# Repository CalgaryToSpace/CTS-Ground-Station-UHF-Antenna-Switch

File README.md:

# CTS-Ground-Station-UHF-Antenna-Switch

PCB and firmware for a ground station UHF antenna switch (between high-power uplink and low-noise downlink, via a single antenna).

This is a high-power UHF antenna switch PCB (for separate RX/TX paths), controlled with automatic TX sensing.

## Status

Rev 1 PCB works and is deployed at the CalgaryToSpace ground station as of 2026-05-26.

Rev 2 PCB is under development, though it is only a small incremental improvement over Rev 1. Main goal with Rev 2 is to improve the isolation performance.

## Render

See the Releases for schematics, gerbers, and BOM.

## Features

* High Power: Supports TX power of >45 dBm (>30 W)
* Low insertion loss
* Automatic carrier sensing on the TX line (easy to deploy)
* Shunt-to-GND: Avoids damage to the transmitter by avoiding reflecting any power back on the TX port, in case of switching latency or failure. Dissipates as heat through a dummy load.
* LED indicators.
* Uses RF relays for switching. Simple design and minimal power supply requirements, compared to PIN Diode alternative approach.
* Logs via USB serial interface.
* Optional slide switch to override control modes.
* Optional control via USB serial interface overrides.

## Key Components

* RF Relay: `1462051-1` (`HF3-1` with 3V control, aka `HF3-51`)
* Dummy Load Resistor: `I100N50X4B`
* RF Attenuator (10 dB): `PAT1220-C-10DB-T5`
* RF Detector: `LTC5507ES6`
* Microcontroller: RP2040-Zero PCB

## License

* **Hardware Parts:** CERN Open Hardware Licence Version 2 - Permissive
* **Firmware:** Apache 2.0 License

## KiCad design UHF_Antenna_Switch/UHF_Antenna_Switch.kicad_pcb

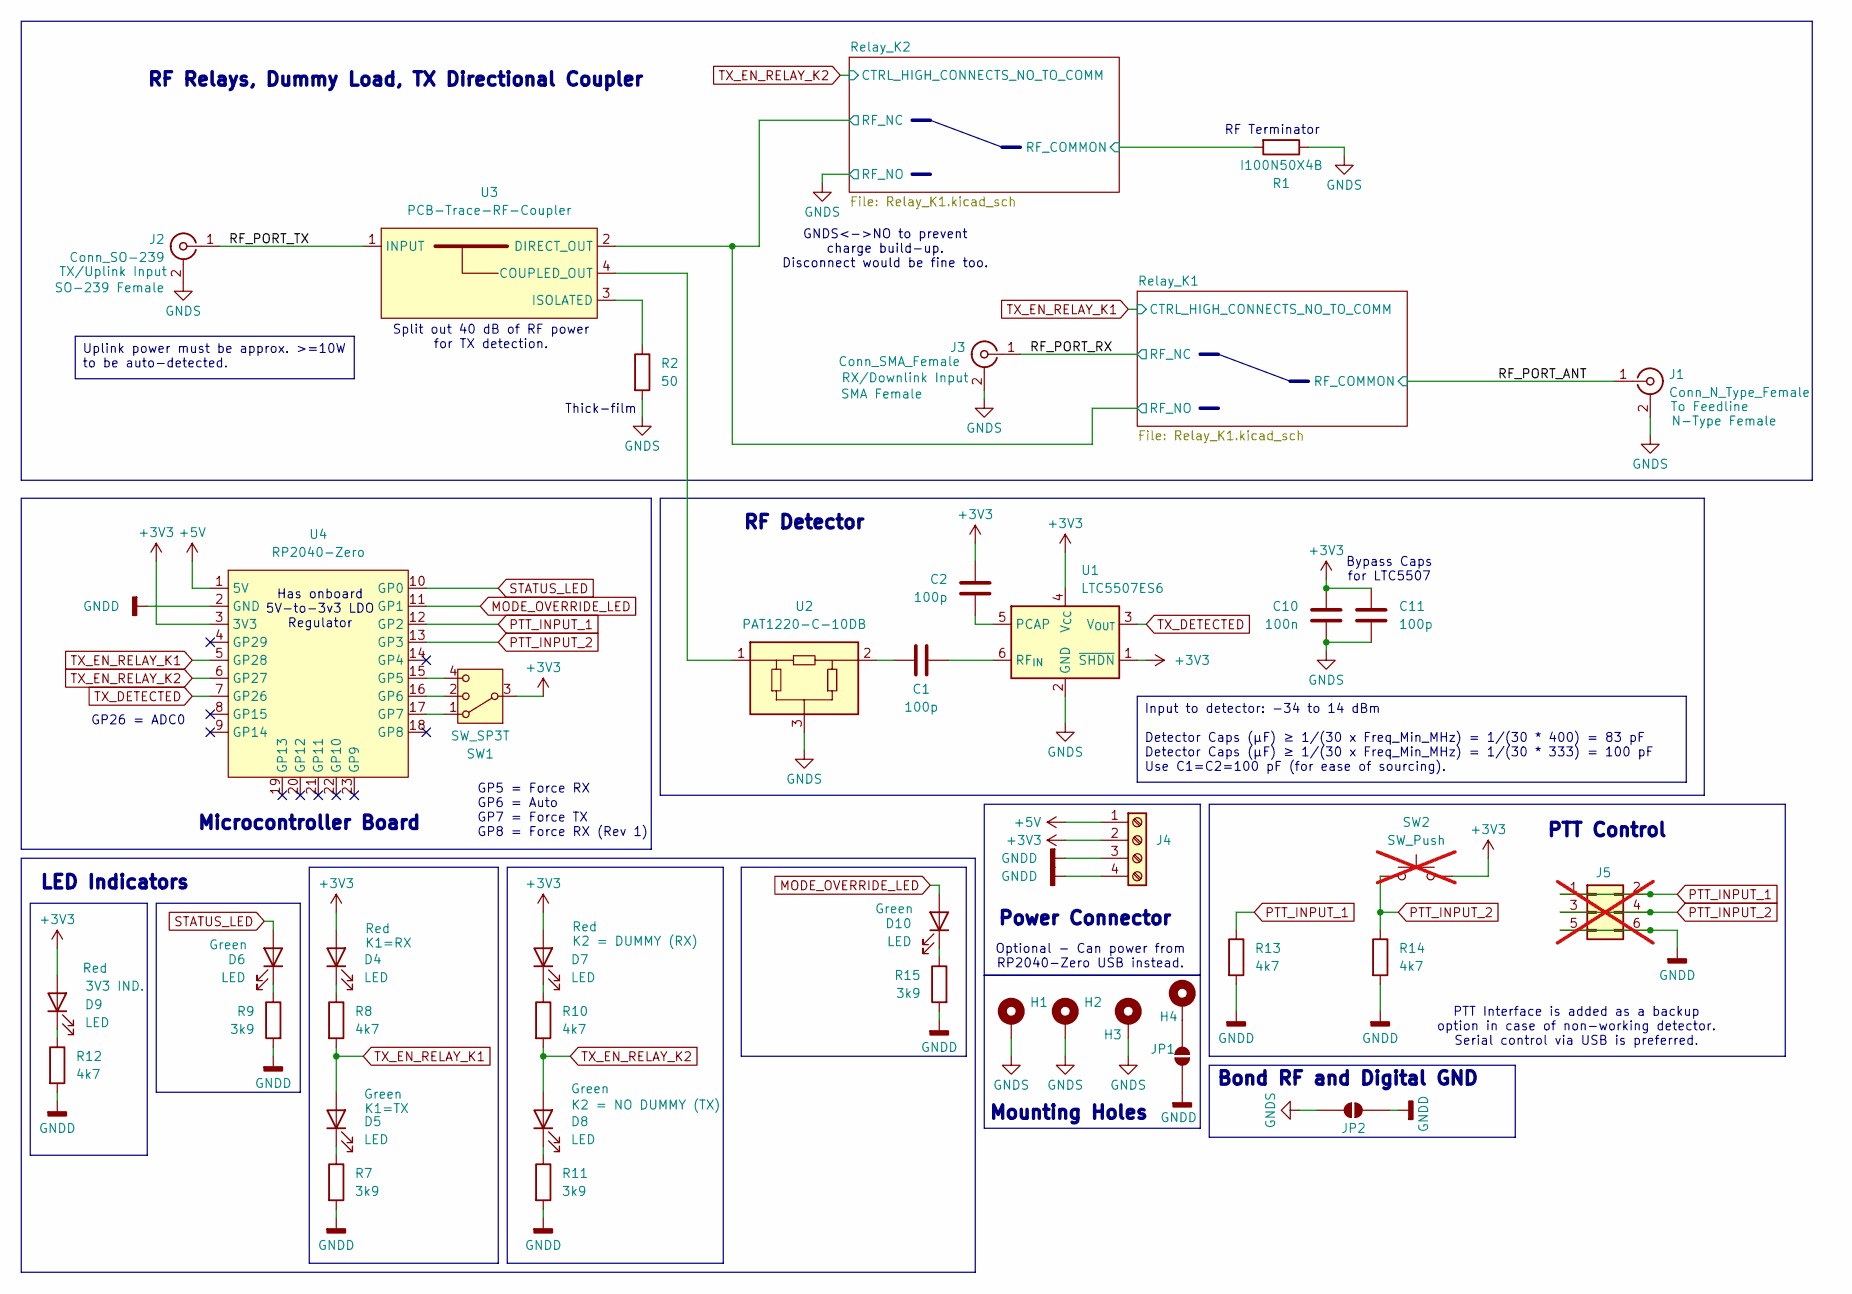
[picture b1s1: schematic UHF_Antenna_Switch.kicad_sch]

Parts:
C1, C2, C11: 100p; C_0603_1608Metric_Pad1.08x0.95mm_HandSolder
C10: 100n; C_0603_1608Metric_Pad1.08x0.95mm_HandSolder
D4, D5, D6, D7, D8, D9, D10: LED; LED_0603_1608Metric_Pad1.05x0.95mm_HandSolder
H1, H2, H3, H4: MountingHole_Pad; MountingHole_3.2mm_M3_Pad
J1: Conn_N_Type_Female; Amphenol N Jack 172234
J2: Conn_SO-239; Amphenol N Jack 172234
J3: Conn_SMA_Female; SMA_Amphenol_901-144_Vertical
J4: Screw_Terminal_01x04; TerminalBlock_Phoenix_MKDS-1,5-4-5.08_1x04_P5.08mm_Horizont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
J5: Conn_02x03_Odd_Even; PinHeader_2x03_P2.54mm_Vertical; not fitted
JP1, JP2: SolderJumper_2_Open; SolderJumper-2_P1.3mm_Open_RoundedPad1.0x1.5mm
R1: I100N50X4B; I100N50X4B-On-PCB
R2: 50; R_0603_1608Metric_Pad0.98x0.95mm_HandSolder
R7, R9, R11, R15: 3k9; R_0603_1608Metric_Pad0.98x0.95mm_HandSolder
R8, R10, R12, R13, R14: 4k7; R_0603_1608Metric_Pad0.98x0.95mm_HandSolder
SW1: SW_SP3T; SW_SP3T_PCM13
SW2: SW_Push; SW_PUSH_6mm_H4.3mm; not fitted
U1: LTC5507ES6; TSOT-23-6_HandSoldering
U2: PAT1220-C-10DB; RF_Attenuator_Susumu_PAT1220
U3: PCB-Trace-RF-Coupler
U4: RP2040-Zero; RP2040 Zero

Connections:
+3V3: C2.1, C10.1, C11.1, D4.2 (A), D7.2 (A), D9.2 (A), J4.2, SW1.3, SW2.2, U1.1 (~SHDN), U1.4 (V_{CC}), U4.3 (3V3); also elsewhere on the board
+5V: J4.1, U4.1 (5V)
/RF_PORT_ANT: J1.1 (In); also elsewhere on the board
/RF_PORT_RX: J3.1 (In); also elsewhere on the board
/RF_PORT_TX: J2.1 (In), U3.1 (INPUT)
/Relay_K1/RF_NO: U3.2 (DIRECT_OUT); also elsewhere on the board
/Relay_K2/RF_COMMON: R1.2; also elsewhere on the board
GNDD: J4.3, J4.4, J5.5, J5.6, JP1.1 (A), JP2.1 (A), R7.2, R9.2, R11.2, R12.2, R13.2, R14.2, R15.2, U4.2 (GND); also elsewhere on the board
GNDS: C10.2, C11.2, H1.1 (1_1), H2.1 (1_1), H3.1 (1_1), J1.2 (Ext), J2.2 (Ext), J3.2 (Ext), JP2.2 (B), R1.1, R2.2, U1.2 (GND), U2.3; also elsewhere on the board
MODE_OVERRIDE_LED: D10.2 (A), U4.11 (GP1)
unnamed: C1.1, U2.2
unnamed: D4.1 (K), R8.1
unnamed: D5.1 (K), R7.1
unnamed: D6.1 (K), R9.1
unnamed: D7.1 (K), R10.1
unnamed: D8.1 (K), R11.1
unnamed: D9.1 (K), R12.1
unnamed: D10.1 (K), R15.1
unnamed: H4.1 (1_1), JP1.2 (B)
unnamed: C2.2, U1.5 (PCAP)
unnamed: C1.2, U1.6 (RF_{IN})
unnamed: U2.1, U3.4 (COUPLED_OUT)
unnamed: R2.1, U3.3 (ISOLATED)
unnamed: SW1.4, U4.15 (GP5)
unnamed: SW1.2, U4.16 (GP6)
unnamed: SW1.1, U4.17 (GP7)
PTT_INPUT_1: J5.1, J5.2, R13.1, U4.12 (GP2)
PTT_INPUT_2: J5.3, J5.4, R14.1, SW2.1, U4.13 (GP3)
STATUS_LED: D6.2 (A), U4.10 (GP0)
TX_DETECTED: U1.3 (V_{OUT}), U4.7 (GP26)
TX_EN_RELAY_K1: D5.2 (A), R8.2, U4.5 (GP28); also elsewhere on the board
TX_EN_RELAY_K2: D8.2 (A), R10.2, U4.6 (GP27); also elsewhere on the board

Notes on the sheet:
Has onboard 5V-to-3v3 LDO Regulator
RF Relays, Dummy Load, TX Directional Coupler
Power Connector
Split out 40 dB of RF power for TX detection.
Mounting Holes
Thick-film
PTT Control
Optional - Can power from RP2040-Zero USB instead.
RF Detector
PTT Interface is added as a backup option in case of non-working detector. Serial control via USB is preferred.
GP26 = ADC0
GNDS<->NO to prevent charge build-up. Disconnect would be fine too.
GP5 = Force RX GP6 = Auto GP7 = Force TX GP8 = Force RX (Rev 1)
Bond RF and Digital GND
Bypass Caps for LTC5507
Microcontroller Board
LED Indicators
RF Terminator
Uplink power must be approx. >=10W to be auto-detected.
Input to detector: -34 to 14 dBm Detector Caps (µF) ≥ 1/(30 x Freq_Min_MHz) = 1/(30 * 400) = 83 pF Detector Caps (µF) ≥ 1/(30 x Freq_Min_MHz) = 1/(30 * 333) = 100 pF Use C1=C2=100 pF (for ease of sourcing).

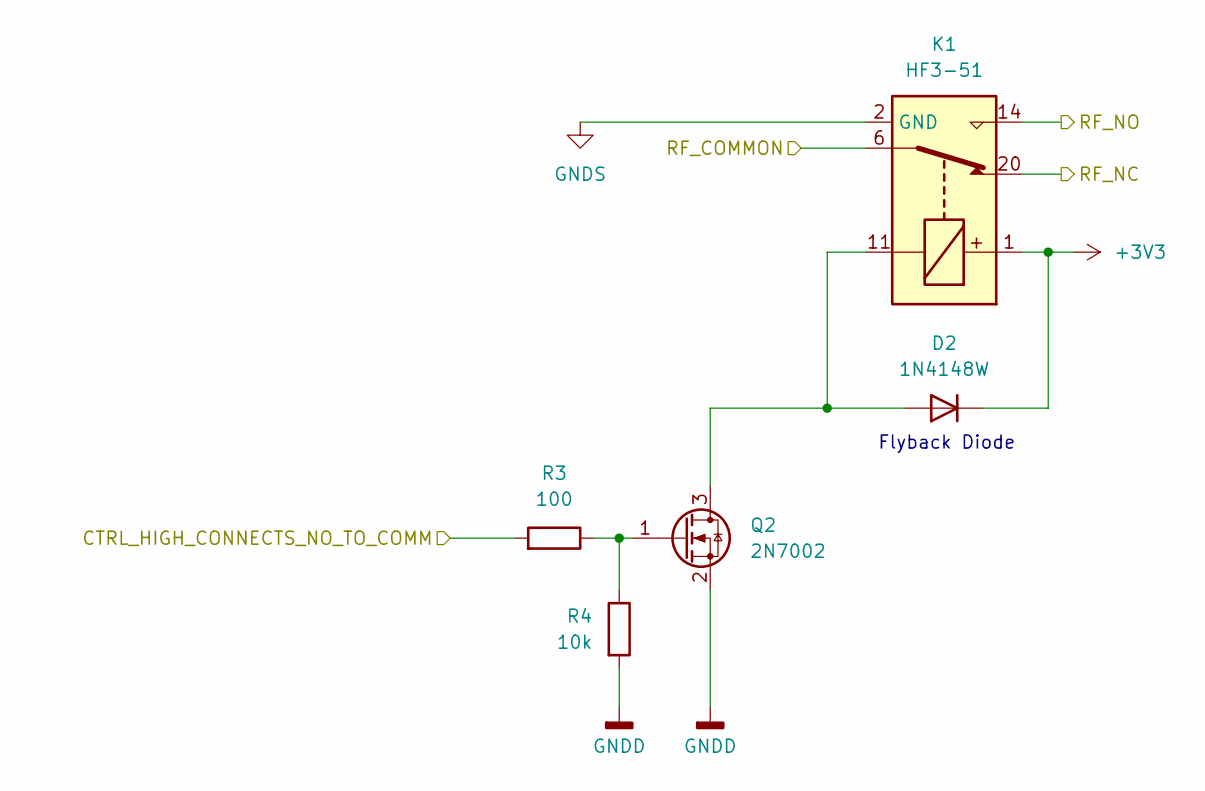
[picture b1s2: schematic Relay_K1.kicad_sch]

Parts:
D2: 1N4148W; D_SOD-123
K1: HF3-51; Relay_SPDT_AXICOM_HF3Series_50ohms_Pitch1.27mm
Q2: 2N7002; SOT-23
R3: 100; R_0603_1608Metric_Pad0.98x0.95mm_HandSolder
R4: 10k; R_0603_1608Metric_Pad0.98x0.95mm_HandSolder

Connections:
+3V3: D2.1 (K), K1.1; also elsewhere on the board
/RF_PORT_ANT: K1.6; also elsewhere on the board
/RF_PORT_RX: K1.20; also elsewhere on the board
/Relay_K1/RF_NO: K1.14; also elsewhere on the board
GNDD: Q2.2 (S), R4.2; also elsewhere on the board
GNDS: K1.2 (GND), K1.5 (GND), K1.7 (GND), K1.10 (GND), K1.12 (GND), K1.13 (GND), K1.15 (GND), K1.17 (GND), K1.19 (GND), K1.21 (GND), K1.22 (GND); also elsewhere on the board
unnamed: D2.2 (A), K1.11, Q2.3 (D)
unnamed: Q2.1 (G), R3.1, R4.1
TX_EN_RELAY_K1: R3.2; also elsewhere on the board

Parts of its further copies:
D3: 1N4148W; D_SOD-123
K2: HF3-51; Relay_SPDT_AXICOM_HF3Series_50ohms_Pitch1.27mm
Q3: 2N7002; SOT-23
R5: 100; R_0603_1608Metric_Pad0.98x0.95mm_HandSolder
R6: 10k; R_0603_1608Metric_Pad0.98x0.95mm_HandSolder

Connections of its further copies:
+3V3: D3.1 (K), K2.1; also elsewhere on the board
/Relay_K1/RF_NO: K2.20; also elsewhere on the board
/Relay_K2/RF_COMMON: K2.6; also elsewhere on the board
GNDD: Q3.2 (S), R6.2; also elsewhere on the board
GNDS: K2.2 (GND), K2.5 (GND), K2.7 (GND), K2.10 (GND), K2.12 (GND), K2.13 (GND), K2.14, K2.15 (GND), K2.17 (GND), K2.19 (GND), K2.21 (GND), K2.22 (GND); also elsewhere on the board
unnamed: D3.2 (A), K2.11, Q3.3 (D)
unnamed: Q3.1 (G), R5.1, R6.1
TX_EN_RELAY_K2: R5.2; also elsewhere on the board

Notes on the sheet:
Flyback Diode

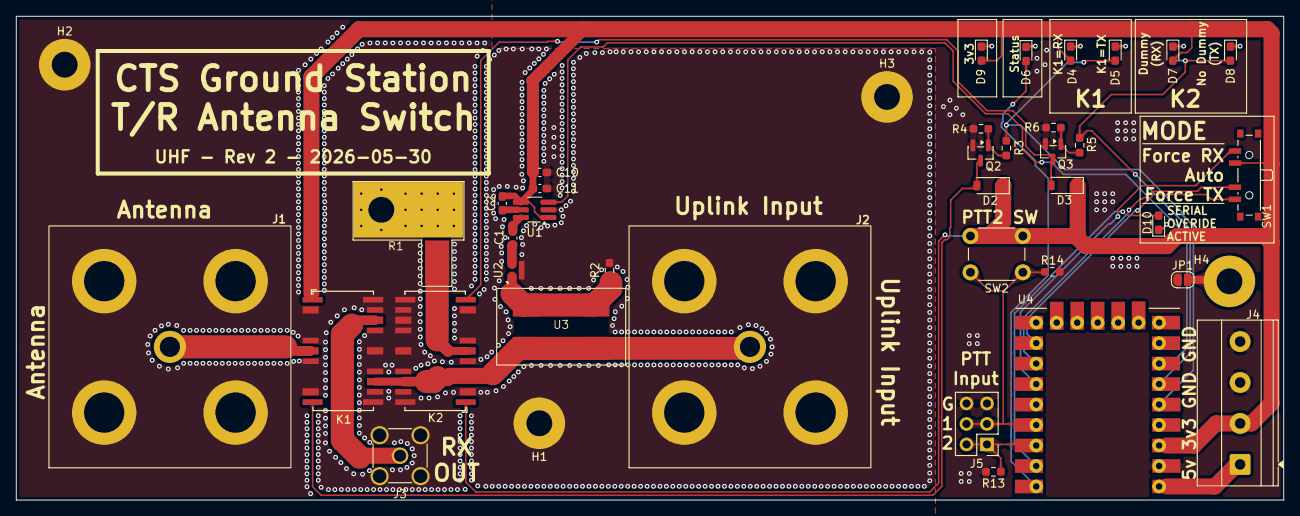
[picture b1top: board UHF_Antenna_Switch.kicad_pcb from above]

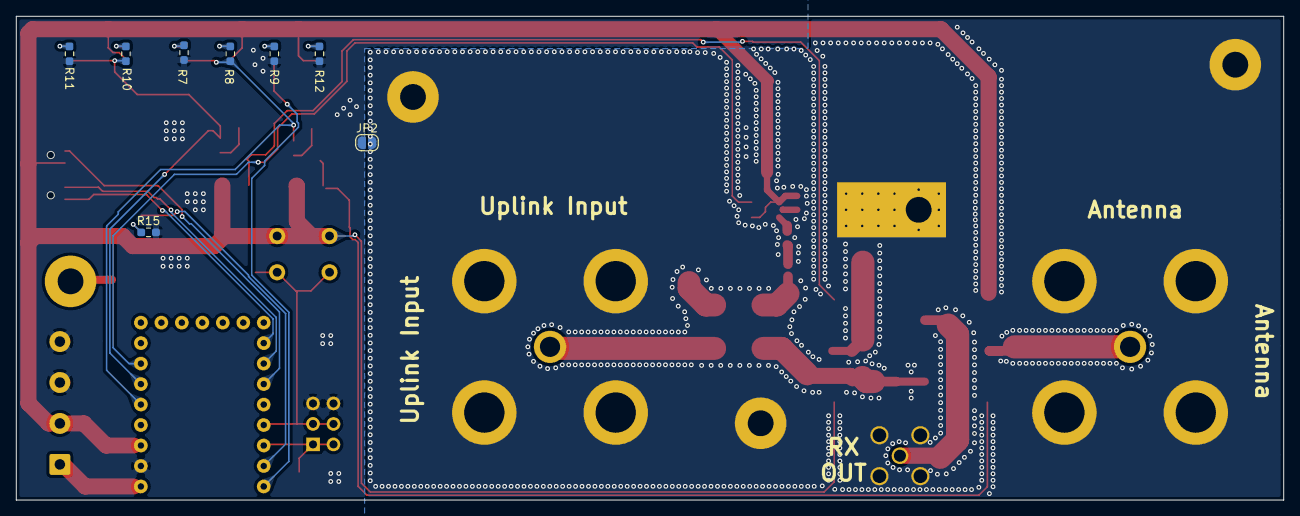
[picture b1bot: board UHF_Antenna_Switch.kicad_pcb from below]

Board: 2 copper layers, 157.2 x 60.0 mm, 49 parts (8 on the bottom side), 36 nets.

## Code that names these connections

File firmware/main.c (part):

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//
// Values are the x in the schematic's GPx pin labels.
// ---------------------------------------------------------------------------
#define PIN_STATUS_LED          0
#define PIN_SERIAL_OVERRIDE_LED 1

#define PIN_MODE_FORCE_RX_REV_2 5
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#define PIN_TX_DETECT_ADC       26   // ADC0
#define ADC_TX_DETECT_CHANNEL   0

#define PIN_TX_EN_RELAY_K1      28   // RX/TX path relay   (LOW = RX path)
#define PIN_TX_EN_RELAY_K2      27   // Dummy load relay   (LOW = dummy applied)

// ---------------------------------------------------------------------------
// Tunables
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    // Sequencing: when entering TX, flip K1 first then K2 (after delay).
    //             when entering RX, flip K2 first then K1 (after delay).
    if (state == RF_TX) {
        gpio_put(PIN_TX_EN_RELAY_K1, 1);
        sleep_ms(RELAY_SWITCH_DELAY_MS);
        gpio_put(PIN_TX_EN_RELAY_K2, 1);
        sleep_ms(RELAY_SWITCH_DELAY_MS); // Critical: Wait for the second relay to stabilize too!
    } else {
        gpio_put(PIN_TX_EN_RELAY_K2, 0);
        sleep_ms(RELAY_SWITCH_DELAY_MS);
        gpio_put(PIN_TX_EN_RELAY_K1, 0);
        sleep_ms(RELAY_SWITCH_DELAY_MS); // Critical: Wait for the second relay to stabilize too!
    }
}
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// Setup
// ---------------------------------------------------------------------------
static void setup_gpio(void) {
    gpio_init(PIN_STATUS_LED);
    gpio_set_dir(PIN_STATUS_LED, GPIO_OUT);
    gpio_put(PIN_STATUS_LED, 0);

    gpio_init(PIN_SERIAL_OVERRIDE_LED);
    gpio_set_dir(PIN_SERIAL_OVERRIDE_LED, GPIO_OUT);
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    }

    // Relay outputs, default LOW (= RX + dummy applied = safe nominal state).
    gpio_init(PIN_TX_EN_RELAY_K1);
    gpio_set_dir(PIN_TX_EN_RELAY_K1, GPIO_OUT);
    gpio_put(PIN_TX_EN_RELAY_K1, 0);

    gpio_init(PIN_TX_EN_RELAY_K2);
    gpio_set_dir(PIN_TX_EN_RELAY_K2, GPIO_OUT);
    gpio_put(PIN_TX_EN_RELAY_K2, 0);
}

static void setup_adc(void) {
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    LOG(LOG_DEBUG, "set_status_led: %d -> %d", status_led_state, state);

    status_led_state = state;
    gpio_put(PIN_STATUS_LED, state);
}

// ---------------------------------------------------------------------------
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
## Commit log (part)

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2026-05-11 Add Licence: CERN Open Hardware Permissive
2026-05-11 docs: Add some design docs
2026-05-11 Add empty KiCAD project
2026-05-11 Schematic: Draw relays and dummy load
2026-05-11 Draw X4C09F1-30S symbol
2026-05-12 Draw relay buffers and detector
2026-05-12 Schematic: Add RP2040 microcontroller and LEDs
2026-05-12 Assign most footprints
2026-05-12 Add N-Type PCB connector footprint
2026-05-12 docs: Add note about footprints
2026-05-12 Add 3V3 power connector
2026-05-12 Add preliminary footprint to directional coupler and begin layout
2026-05-12 Rename X4C09F1-30S footprint with no space
2026-05-12 Configure net classes and trace widths
2026-05-13 Complete initial positioning of components (no routing)
2026-05-13 Swap to SP4T switch
2026-05-13 Schematic: Add PTT switches, PTT header, 5V power screw
2026-05-13 Re-add net class configs
2026-05-13 Footprint: Draw RF coupler with microstrip
2026-05-13 PCB: Route RF components
2026-05-14 PCB: Route digital components
2026-05-14 PCB: Add many labels
2026-05-14 PCB: Fix keepout region on Trace RF Coupler
2026-05-14 PCB: Resolve DRC issues
2026-05-14 PCB: Add 4th mounting hole
2026-05-14 Bond RF and Digital GNDs
2026-05-14 Export rc1 gerber
2026-05-14 Resave after exporting Rev 1 gerber
2026-05-14 docs: Add PCB Render to repo
2026-05-14 Implement firmware
2026-05-14 build: Auto-download the Pico SDK on build
2026-05-14 feat: Review logging and delay behaviour
2026-05-15 build: Enable -O3 build optimization
2026-05-15 fix: Bad RF detection threshold
2026-05-18 feat: Add hardware watchdog for reliability
2026-05-23 docs: Add Calibration.md guide
2026-05-23 docs: Add basic PCB Test Plan
2026-05-23 fix: Build was failing on latest picotool version
2026-05-23 feat: Show log levels in messages, add heartbeat INFO log
2026-05-23 docs: Add details to Basic Bring-Up test plan
2026-05-26 feat: Add Tx/Rx serial override commands
2026-05-26 config: Set relay latency to 12ms
2026-05-26 chore: Add cmake temp files to gitignore
2026-05-27 fix(pcb): Jagged gnd plane shard
2026-05-27 chore(pcb): Add LED colors, update LED resistor values
2026-05-27 fix(pcb): Add silkscreen labels for RF ports on backside
2026-05-27 fix(pcb): Make attenuator gnd pad solid
2026-05-27 ci: Add firmware build GitHub Action
2026-05-27 ci: Fix failing build on first attempt
2026-05-27 Silence output a bit
2026-05-27 bump action version
2026-05-27 ci: Add firmware build GitHub Action (#8)
2026-05-27 fix(pcb): Add vias for heat dissipation under dummy load attenuator
2026-05-27 feat(fw): Show reason for mode better
2026-05-27 feat(fw): Add help menu, reboot commands
2026-05-27 feat(fw): Add banner on USB connection opened
2026-05-27 docs: Add firmware license, update feature list/README
2026-05-27 tiny(pcb): Move K1 down
2026-05-27 PCB: Try adding 3rd relay to increase port isolation
2026-05-27 chore(pcb): Minor layout tweaks in RF area
2026-05-27 feat(pcb): Add tons of fencing vias
2026-05-30 feat: Add Serial Override LED indicator
2026-05-30 fix(pcb): Swap order of mode switch items
2026-05-30 feat(fw): Add serial override LED and Rev 2 switch support
2026-05-30 feat(fw): Add build timestamp/commit to header
2026-05-30 feat(pcb): Finish Rev 2 render, exports
2026-06-02 fix(pcb): DRC rule about intentional shorted nets in RF coupler
2026-06-23 docs: Add Rev 1 vs. Rev 2 isolation comparison
